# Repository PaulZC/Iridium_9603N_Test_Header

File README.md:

# Iridium 9603N Test Header

A test header which mimics the Iridium 9603N, to aid circuit board debugging. Fitted with a Samtec ST4-10-2.50.

## Repository Contents
- **/Hardware** - Eagle schematic and PCB design files
- **LICENSE.md** contains the licence information

Enjoy!

**_Paul_**

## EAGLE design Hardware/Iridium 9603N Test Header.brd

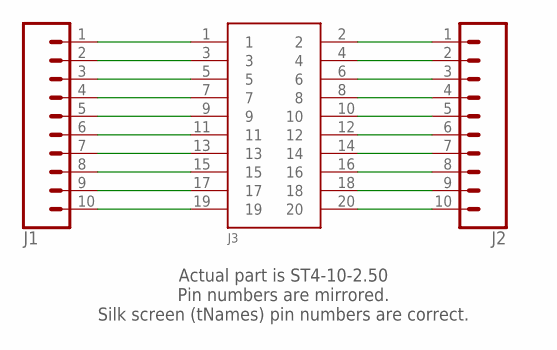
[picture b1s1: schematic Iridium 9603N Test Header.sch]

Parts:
J1, J2: CONN_10"; 1X10
J3: SS4-10-3.50-X-D

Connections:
unnamed: J1.1, J3.1
unnamed: J1.2, J3.3
unnamed: J1.3, J3.5
unnamed: J1.4, J3.7
unnamed: J1.5, J3.9
unnamed: J1.6, J3.11
unnamed: J1.7, J3.13
unnamed: J1.8, J3.15
unnamed: J1.9, J3.17
unnamed: J1.10, J3.19
unnamed: J2.10, J3.20
unnamed: J2.9, J3.18
unnamed: J2.8, J3.16
unnamed: J2.7, J3.14
unnamed: J2.6, J3.12
unnamed: J2.5, J3.10
unnamed: J2.4, J3.8
unnamed: J2.3, J3.6
unnamed: J2.2, J3.4
unnamed: J2.1, J3.2

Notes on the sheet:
Actual part is ST4-10-2.50 Pin numbers are mirrored. Silk screen (tNames) pin numbers are correct.

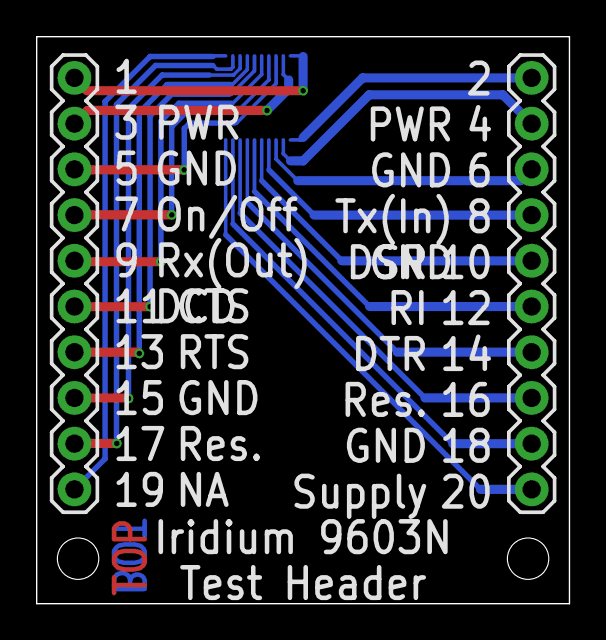
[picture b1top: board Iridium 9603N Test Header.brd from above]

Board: 2 copper layers, 29.6 x 31.5 mm, 3 parts (1 on the bottom side), 20 nets.

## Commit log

2019-10-16 Fixed the README
2019-10-16 Added the dimensions
2019-11-01 Corrected the ST4-10-2.50 footprint

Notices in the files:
parts and their libraries:
SparkFun-Connectors: Licensing: Creative Commons ShareAlike 4.0 International - https://creativecommons.org/licenses/by-sa/4.0
